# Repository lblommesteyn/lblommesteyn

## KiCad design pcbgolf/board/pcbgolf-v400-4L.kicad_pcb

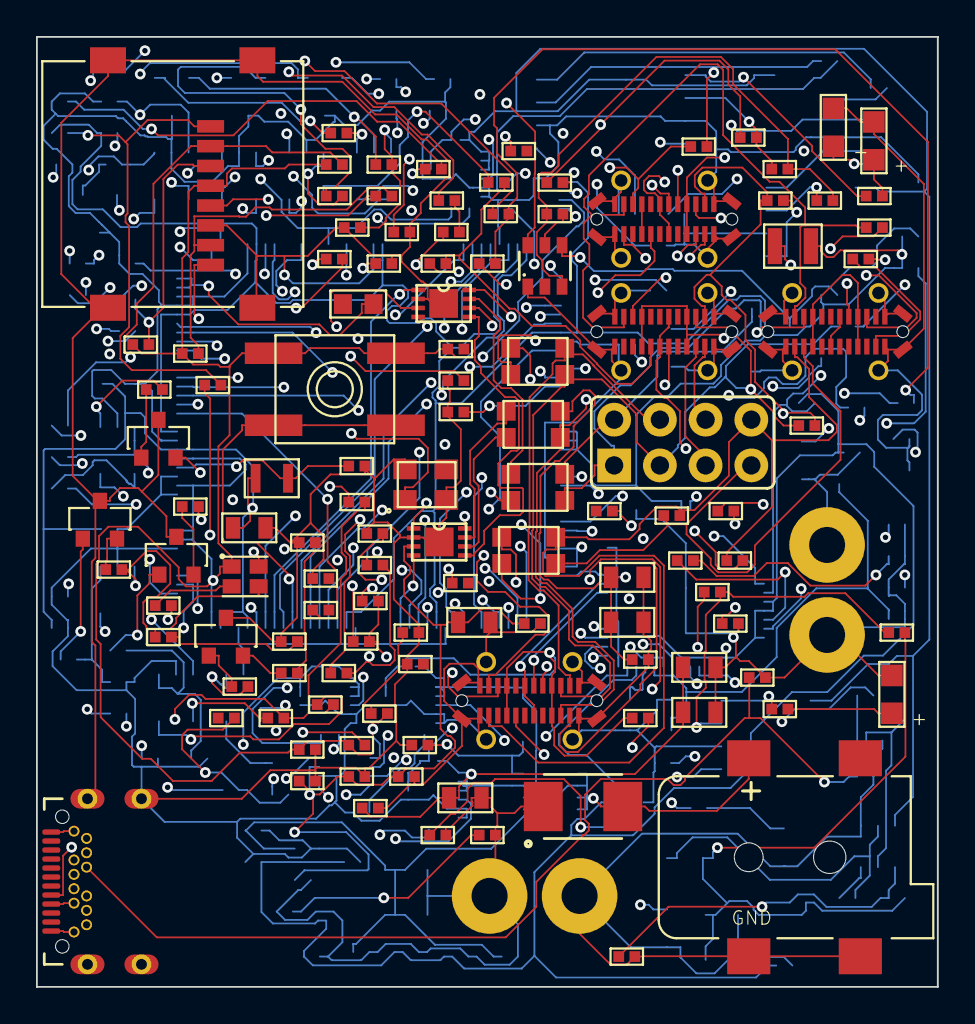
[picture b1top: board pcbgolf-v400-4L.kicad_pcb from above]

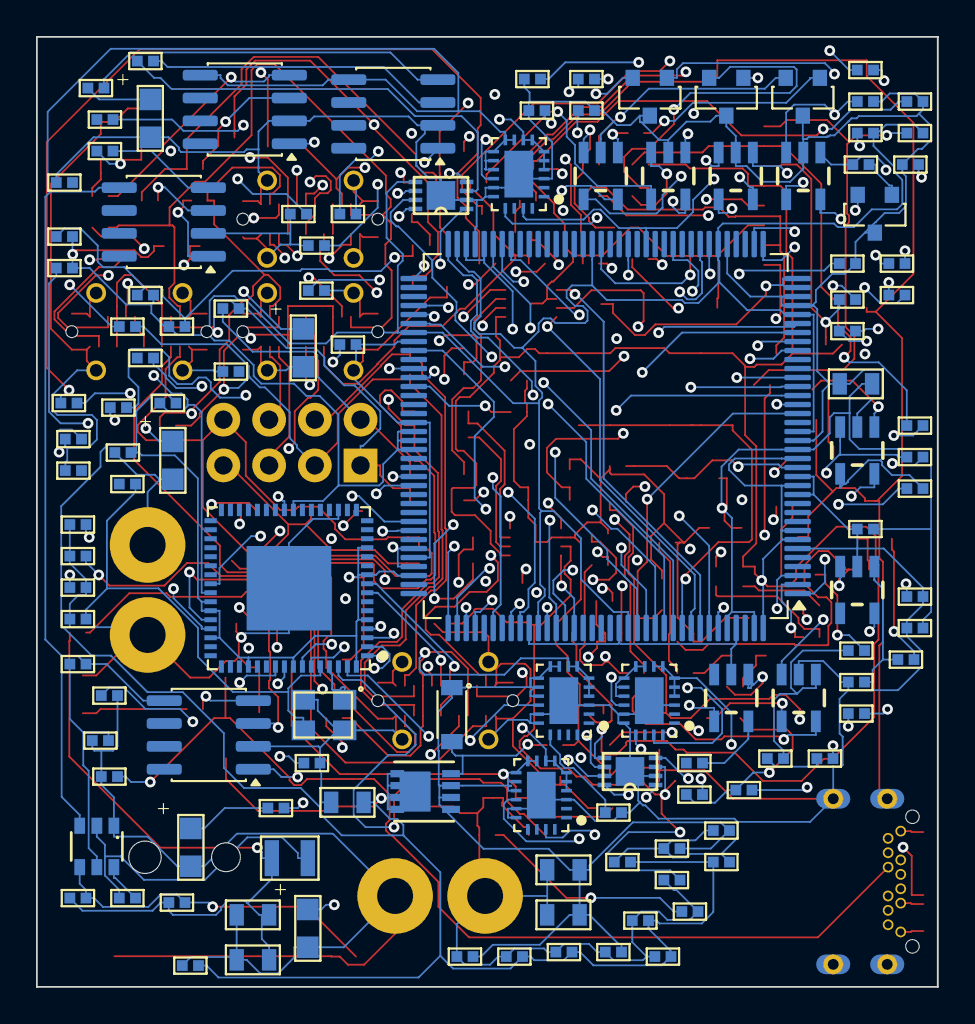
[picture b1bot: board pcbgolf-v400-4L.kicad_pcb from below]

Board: 4 copper layers, 50.0 x 52.8 mm, 245 parts (123 on the bottom side), 196 nets.

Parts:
BH1, BH2, BH3, BH4: M2_BOLT
C1, C3, C8, C12, C13, C15, C19, C20, C21: 10uF; 0805-C
C2, C4, C5, C7, C9, C11, C16, C18, C22, C23, C24, C26, C27, C30, C31, C35, C36, C38, C39, C40, C41, C42, C43, C44, C45, C46, C47, C48, C49: 100nF; 0402-C
C6, C10: DNP; 0402-C
C14, C17, C28, C32: 12pF; 0402-C
C25: 220pF; 0402-C
C29, C33, C34, C37: 10u; 0402-C
C50, C51, C52, C53: 10u; 0805-C
D1: TVS-BI-DO214AA; DO-214AA(SMB)
D2: DIODEDB2W40100L; SOD-123F
J1: DCBARRELSMT; DCJACK_2MM_SMT
J2: MICRO_SD-0472192001; 0472192001
J3: USB-C-FEMALE; DX07S024XJ1R1100
J4: CAN; 2X04
J5, J6, J7, J8: USB-C-FEMALEGCT; USB-C-FEMALE-VERT-GCT
L1, L2: 3u3; L-1008
L3: L-US-L2; 0603-L
L4: 2u2; 0806
L5, L6, L7, L8: ACT1210D_CHOKE; CHOKE-3.2X2.5
LED1: CREE-RGB-CLMVC
LED2: CAN0; CHIPLED
LED3: CAN1; CHIPLED
LED4: CAN2; CHIPLED
LED5: CAN3; CHIPLED
LED6, LED7, LED8, LED9: CH1_PWR; CHIPLED
LED10, LED11, LED12, LED13, LED14, LED15, LED16, LED17: LED-CC-GREEN-RED-AM23ESG; SOT23-3
Q1: SIS427-VI; PP-1212-8
Q2, Q3, Q4, Q5, Q6, Q7, Q8, Q9: NFET-DUAL-COMMON-SOURCE-QS5K2; SOT23-5
R1, R3, R7, R8, R9, R11, R12, R28, R29, R30, R31, R32, R33, R34, R35, R36, R37, R44, R45, R50, R51, R53, R54, R56, R57, R59, R60, R78, R79, R80, R81, R98, R99, R100, R101, R102, R103, R104, R105, R122, R123, R124, R125: 10k; 0402-R
R2, R21, R23, R90, R92, R94, R96, R114, R116, R118, R120: 1k; 0402-R
R4, R5, R6, R13, R14, R15, R16, R17, R18, R19, R20, R24, R25, R52, R55, R58, R61: 100k; 0402-R
R10: 52k3; 0402-R
R22, R62, R63, R64, R65: 2k7; 0402-R
R26: 1M; 0402-R
R27: 12k; 0402-R
R38, R39, R40, R41, R42, R43: 0R; 0402-R
R46, R47, R48, R49: 60; 0402-R
R66, R67, R68, R69: 28k; 0402-R
R70, R71, R72, R73: 33k; 0402-R
R74, R75, R76, R77: 3k3; 0402-R
R82, R83, R84, R85, R86, R87, R88, R89, R91, R93, R95, R97, R106, R107, R108, R109, R110, R111, R112, R113, R115, R117, R119, R121: 100; 0402-R
SW1: SPST-2-4PIN; EVQ-Q2
U1, U2: AP62300T; SOT23-6
U3: STM32H725ZGTx; LQFP-144_20x20mm_P0.5mm
U4: USB2517; QFN64-9X9
U5, U6, U7, U8: MCP2542FDT-E/MNY; TDFN8_2X3MC_MCH
U9, U10, U11, U12: NCS20071XV; SOIC-8_3.9x4.9mm_P1.27mm
U13, U14, U15, U16: TPS25942; WQFN20
Y1: 25MHz; XTAL-3.2X2.5
Y2: 24MHz; XTAL-3.2X2.5

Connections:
+3V3: C6.2, C7.1, C8.1, C19.1, C20.1, C23.1, C24.1, C26.1, C27.1, C30.2, C31.2, C37.1, C42.1, C43.1, C44.1, C45.1, J2.4 (VDD), L1.2, L3.1, LED1.U1 (COM+), R4.1, R5.1, R6.1, R11.1, R28.1, R29.1, R30.1, R33.1, R34.1, R35.1, R36.1, R37.1, SW1.B (S), SW1.B' (S1), U3.7 (VDD), U3.8 (VBAT), U3.13 (VDD), U3.16 (VDDSMPS), U3.19 (VDD), U3.32 (VDD), U3.42 (VDD), U3.56 (VDD), U3.71 (VDD), U3.79 (VDD), U3.90 (VDD50USB), U3.91 (VDD33USB), U3.92 (VDD), U3.106 (VDD), U3.119 (VDD), U3.129 (VDD), U3.144 (VDD), U4.5 (VDDA33), U4.10 (VDDA33), U4.13 (CFG_SEL2), U4.24 (VDD33CR), U4.42 (CFG_SEL1), U4.43 (RESET_N), U4.46 (VDD33), U4.52 (VDDA33), U4.57 (VDDA33), U4.64 (VDD33PLL), U5.5 (VIO), U6.5 (VIO), U7.5 (VIO), U8.5 (VIO)
+5V: C1.1, C2.1, C10.2, C11.1, C12.1, C13.1, C38.1, C39.1, C40.1, C41.1, L2.2, R1.1, R10.2, R52.2, R55.2, R58.2, R61.2, U1.3 (IN), U5.3 (VDD), U6.3 (VDD), U7.3 (VDD), U8.3 (VDD)
+12V: C3.1, C5.1, C46.1, C47.1, C48.1, C49.1, C50.1, C51.1, C52.1, C53.1, D2.1 (C), Q1.1 (S), Q1.2 (S), Q1.3 (S), R7.1, U2.3 (IN), U9.5 (V+), U10.5 (V+), U11.5 (V+), U12.5 (V+), U13.9 (VIN), U13.10 (VIN), U13.11 (VIN), U13.12 (VIN), U13.13 (VIN), U14.9 (VIN), U14.10 (VIN), U14.11 (VIN), U14.12 (VIN), U14.13 (VIN), U15.9 (VIN), U15.10 (VIN), U15.11 (VIN), U15.12 (VIN), U15.13 (VIN), U16.9 (VIN), U16.10 (VIN), U16.11 (VIN), U16.12 (VIN), U16.13 (VIN)
BTN: R12.2, SW1.A, SW1.A' (P1), U3.65 (PE15), U3.135 (BOOT0)
CAN0_EN: U3.134 (PB7), U5.8 (STBY)
CAN0_H: J4.2, J5.A2 (TX1+), J6.A2 (TX1+), J7.A2 (TX1+), J8.A2 (TX1+), L5.4, R46.2, R50.1
CAN0_L: J4.1, J5.A3 (TX1-), J6.A3 (TX1-), J7.A3 (TX1-), J8.A3 (TX1-), L5.3, R46.1, R51.1
CAN0_RX: U3.136 (PB8), U5.4 (RXD)
CAN0_TX: U3.137 (PB9), U5.1 (TXD)
CAN1_EN: U3.130 (PB3(JTDO), U6.8 (STBY)
CAN1_H: J4.4, J5.A11 (RX2+), J6.A11 (RX2+), J7.A11 (RX2+), J8.A11 (RX2+), L6.4, R47.2, R53.1
CAN1_L: J4.3, J5.A10 (RX2-), J6.A10 (RX2-), J7.A10 (RX2-), J8.A10 (RX2-), L6.3, R47.1, R54.1
CAN1_RX: U3.132 (PB5), U6.4 (RXD)
CAN1_TX: U3.133 (PB6), U6.1 (TXD)
CAN2_EN: U3.121 (PD7), U7.8 (STBY)
CAN2_H: J4.6, J5.B2 (TX2+), J6.B2 (TX2+), J7.B2 (TX2+), J8.B2 (TX2+), L7.4, R48.2, R56.1
CAN2_L: J4.5, J5.B3 (TX2-), J6.B3 (TX2-), J7.B3 (TX2-), J8.B3 (TX2-), L7.3, R48.1, R57.1
CAN2_RX: U3.123 (PG10), U7.4 (RXD)
CAN2_TX: U3.122 (PG9), U7.1 (TXD)
CAN3_EN: U3.131 (PB4(NJTRST)), U8.8 (STBY)
CAN3_H: J4.8, J5.B11 (RX1+), J6.B11 (RX1+), J7.B11 (RX1+), J8.B11 (RX1+), L8.4, R49.2, R59.1
CAN3_L: J4.7, J5.B10 (RX1-), J6.B10 (RX1-), J7.B10 (RX1-), J8.B10 (RX1-), L8.3, R49.1, R60.1
CAN3_RX: U3.72 (PB12), U8.4 (RXD)
CAN3_TX: U3.73 (PB13), U8.1 (TXD)
CH1_D_N: J5.A7 (D-A), J5.B7 (D-B), U4.1 (USBDN1_DM)
CH1_D_P: J5.A6 (D+A), J5.B6 (D+B), U4.2 (USBDN1_DP)
CH1_IMON: R70.2, U3.47 (PC4), U13.19 (IMON)
CH1_PWR_EN: U3.37 (PA0), U13.14 (EN)
CH1_SBU1: J5.A8 (SBU1), R19.2, R90.2, R91.2
CH1_SBU1_IGN: Q2.1 (G1), R78.1, R83.2, U3.112 (PD0)
CH1_SBU1_RELAY: Q2.3 (G2), R82.2, R98.2, U3.113 (PD1)
CH1_SBU2: J5.B8 (SBU2), R20.2, R114.2, R115.2
CH1_SBU2_IGN: Q6.1 (G1), R102.1, R107.2, U3.115 (PD3)
CH1_SBU2_RELAY: Q6.3 (G2), R106.2, R122.2, U3.116 (PD4)
CH2_D_N: J6.A7 (D-A), J6.B7 (D-B), U4.3 (USBDN2_DM)
CH2_D_P: J6.A6 (D+A), J6.B6 (D+B), U4.4 (USBDN2_DP)
CH2_IMON: R71.2, U3.50 (PB1), U14.19 (IMON)
CH2_PWR_EN: U3.38 (PA1), U14.14 (EN)
CH2_SBU1: J6.A8 (SBU1), R15.2, R92.2, R93.2
CH2_SBU1_IGN: Q3.1 (G1), R79.1, R85.2, U3.117 (PD5)
CH2_SBU1_RELAY: Q3.3 (G2), R84.2, R99.2, U3.120 (PD6)
CH2_SBU2: J6.B8 (SBU2), R13.2, R116.2, R117.2
CH2_SBU2_IGN: Q7.1 (G1), R103.1, R109.2, U3.76 (PD8)
CH2_SBU2_RELAY: Q7.3 (G2), R108.2, R123.2, U3.78 (PD10)
CH3_D_N: J7.A7 (D-A), J7.B7 (D-B), U4.6 (USBDN3_DM)
CH3_D_P: J7.A6 (D+A), J7.B6 (D+B), U4.7 (USBDN3_DP)
CH3_IMON: R72.2, U3.52 (PF11), U15.19 (IMON)
CH3_PWR_EN: U3.43 (PA4), U15.14 (EN)
CH3_SBU1: J7.A8 (SBU1), R17.2, R94.2, R95.2
CH3_SBU1_IGN: Q4.1 (G1), R80.1, R87.2, U3.82 (PD12)
CH3_SBU1_RELAY: Q4.3 (G2), R86.2, R100.2, U3.81 (PD11)
CH3_SBU2: J7.B8 (SBU2), R18.2, R118.2, R119.2
CH3_SBU2_IGN: Q8.1 (G1), R104.1, R111.2, U3.77 (PD9)
CH3_SBU2_RELAY: Q8.3 (G2), R110.2, R124.2, U3.83 (PD13)
CH4_D_N: J8.A7 (D-A), J8.B7 (D-B), U4.8 (USBDN4_DM)
CH4_D_P: J8.A6 (D+A), J8.B6 (D+B), U4.9 (USBDN4_DP)
CH4_IMON: R73.2, U3.45 (PA6), U16.19 (IMON)
CH4_PWR_EN: U3.44 (PA5), U16.14 (EN)
CH4_SBU1: J8.A8 (SBU1), R16.2, R96.2, R97.2
CH4_SBU1_IGN: Q5.1 (G1), R81.1, R89.2, U3.84 (PD14)
CH4_SBU1_RELAY: Q5.3 (G2), R88.2, R101.2, U3.85 (PD15)
CH4_SBU2: J8.B8 (SBU2), R14.2, R120.2, R121.2
CH4_SBU2_IGN: Q9.1 (G1), R105.1, R113.2, U3.138 (PE0)
CH4_SBU2_RELAY: Q9.3 (G2), R112.2, R125.2, U3.139 (PE1)
GND: BH1.0 (1_0), BH2.0 (1_0), BH3.0 (1_0), BH4.0 (1_0), C1.2, C2.2, C3.2, C5.2, C7.2, C8.2, C11.2, C12.2, C13.2, C14.2, C15.2, C16.2, C17.2, C18.2, C19.2, C20.2, C21.2, C22.2, C23.2, C24.2, C25.2, C26.2, C27.2, C28.2, C29.2, C30.1, C31.1, C32.2, C33.2, C34.2, C35.1, C36.1, C37.2, C38.2, C39.2, C40.2, C41.2, C42.2, C43.2, C44.2, C45.2, C46.2, C47.2, C48.2, C49.2, C50.2, C51.2, C52.2, C53.2, D1.1, J1.GND (GNDBREAK), J1.GNDBREAK (GND), J2.6 (VSS), J2.G1 (GND), J2.G2 (GND), J2.G3 (GND), J2.G4 (GND), J3.A1 (GND), J3.A12 (GND), J3.B1 (GND), J3.B1T (GND), J3.B12 (GND), J3.B12T (GND), J3.S1B (SHIELDA), J3.S1T (SHIELDA), J3.S1TH (SHIELDA), J3.S2B (SHIELDA), J3.S2T (SHIELDA), J3.S2TH (SHIELDA), J3.S3B (SHIELDB), J3.S3T (SHIELDB), J3.S3TH (SHIELDB), J3.S4B (SHIELDB), J3.S4T (SHIELDB), J3.S4TH (SHIELDB), J5.A1 (GND), J5.A12 (GND), J5.B1 (GND), J5.B12 (GND), J5.S1 (SHIELDA), J5.S2 (SHIELDA), J5.S3 (SHIELDA), J5.S4 (SHIELDA), J5.S11 (SHIELDB), J5.S12 (SHIELDB), J5.S13 (SHIELDB), J5.S14 (SHIELDB), J6.A1 (GND), J6.A12 (GND), J6.B1 (GND), J6.B12 (GND), J6.S1 (SHIELDA), J6.S2 (SHIELDA), J6.S3 (SHIELDA), J6.S4 (SHIELDA), J6.S11 (SHIELDB), J6.S12 (SHIELDB), J6.S13 (SHIELDB), J6.S14 (SHIELDB), J7.A1 (GND), J7.A12 (GND), J7.B1 (GND), J7.B12 (GND), J7.S1 (SHIELDA), J7.S2 (SHIELDA), J7.S3 (SHIELDA), J7.S4 (SHIELDA), J7.S11 (SHIELDB), J7.S12 (SHIELDB), J7.S13 (SHIELDB), J7.S14 (SHIELDB), J8.A1 (GND), J8.A12 (GND), J8.B1 (GND), J8.B12 (GND), J8.S1 (SHIELDA), J8.S2 (SHIELDA), J8.S3 (SHIELDA), J8.S4 (SHIELDA), J8.S11 (SHIELDB), J8.S12 (SHIELDB), J8.S13 (SHIELDB), J8.S14 (SHIELDB), LED2.C, LED3.C, LED4.C, LED5.C, LED6.C, LED7.C, LED8.C, LED9.C, LED10.3 (C), LED11.3 (C), LED12.3 (C), LED13.3 (C), LED14.3 (C), LED15.3 (C), LED16.3 (C), LED17.3 (C), Q2.2 (S), Q3.2 (S), Q4.2 (S), Q5.2 (S), Q6.2 (S), Q7.2 (S), Q8.2 (S), Q9.2 (S), R2.1, R3.2, R8.2, R9.2, R12.1, R25.1, R27.1, R31.2, R32.2, R44.2, R45.2, R66.1, R67.1, R68.1, R69.1, R70.1, R71.1, R72.1, R73.1, R78.2, R79.2, R80.2, R81.2, R98.1, R99.1, R100.1, R101.1, R102.2, R103.2, R104.2, R105.2, R122.1, R123.1, R124.1, R125.1, U1.1 (GND), U2.1 (GND), U3.6 (VSS), U3.12 (VSS), U3.14 (VSSSMPS), U3.18 (VSS), U3.33 (VSS), U3.34 (VSSA), U3.41 (VSS), U3.55 (VSS), U3.69 (VSS), U3.80 (VSS), U3.89 (VSS), U3.104 (VSS), U3.118 (VSS), U3.128 (VSS), U3.141 (VSS), U4.19 (TEST), U4.PAD (VSS), U5.2 (VSS), U5.PAD (EPAD), U6.2 (VSS), U6.PAD (EPAD), U7.2 (VSS), U7.PAD (EPAD), U8.2 (VSS), U8.PAD (EPAD), U9.2 (V-), U10.2 (V-), U11.2 (V-), U12.2 (V-), U13.3 (PGTH), U13.15 (OVP), U13.16 (GND), U13.PAD (GND), U14.3 (PGTH), U14.15 (OVP), U14.16 (GND), U14.PAD (GND), U15.3 (PGTH), U15.15 (OVP), U15.16 (GND), U15.PAD (GND), U16.3 (PGTH), U16.15 (OVP), U16.16 (GND), U16.PAD (GND), Y1.2 (3), Y1.4 (3), Y2.2 (3), Y2.4 (3)
HUB_SCL: R30.2, U3.66 (PB10), U4.41 (SCL)
HUB_SDA: R28.2, U3.67 (PB11), U4.40 (SDA)
LED_B: R23.2, U3.1 (PE2)
LED_G: R22.2, U3.2 (PE3)
LED_R: R21.2, U3.3 (PE4)
unnamed: D1.2, J1.PWR1 (PWR), Q1.5 (D), Q1.6 (D), Q1.7 (D), Q1.8 (D), Q1.9 (D)
unnamed: C9.1, U2.6 (BST)
unnamed: C9.2, L2.1, U2.2 (SW)
unnamed: R1.2, U1.5 (EN)
unnamed: C4.2, L1.1, U1.2 (SW)
unnamed: C6.1, R3.1, R4.2, R5.2, R6.2, U1.4 (FB)
unnamed: C4.1, U1.6 (BST)
unnamed: D2.2 (A), Q1.4 (G), R2.2
unnamed: R7.2, R8.1, U2.5 (EN)
unnamed: C10.1, R9.1, R10.1, U2.4 (FB)
unnamed: LED1.U2 (R-), R21.1
unnamed: LED1.U3 (G-), R22.1
unnamed: LED1.U4 (B-), R23.1
unnamed: C14.1, U3.25 (PH0), Y1.1
unnamed: R13.1, U3.21 (PF7)
unnamed: R14.1, U3.22 (PF8)
unnamed: R15.1, U3.23 (PF9)
unnamed: R16.1, U3.24 (PF10)
unnamed: C17.1, U3.26 (PH1), Y1.3 (2)
unnamed: R17.1, U3.28 (PC0)
unnamed: R18.1, U3.29 (PC1)
unnamed: R19.1, U3.30 (PC2_C)
unnamed: R20.1, U3.31 (PC3_C)
unnamed: R11.2, U3.142 (PDR_ON)
unnamed: C33.1, C35.2, U4.25 (VDD18)
unnamed: R24.1, R25.2, U4.44 (VBUS_DET)
unnamed: R29.2, U4.45 (SUSP_IND)
unnamed: C32.1, R26.1, U4.60 (XTAL2), Y2.3 (2)
unnamed: C28.1, R26.2, U4.61 (XTAL1), Y2.1
unnamed: C34.1, C36.2, U4.62 (VDD18PLL)
unnamed: R27.2, U4.63 (RBIAS)
unnamed: J3.A5 (CC1), R31.1, R32.1
unnamed: J3.B2 (TX2+), J3.B2T (TX2+)
unnamed: J3.B3 (TX2-), J3.B3T (TX2-)
unnamed: J3.B5 (CC2), J3.B5T (CC2), R44.1, R45.1
unnamed: J3.B8 (SBU2), J3.B8T (SBU2)
unnamed: J3.B10 (RX1-), J3.B10T (RX1-)
unnamed: J3.B11 (RX1+), J3.B11T (RX1+)
unnamed: J2.7 (DAT0), R33.2, R38.2
unnamed: J2.8 (DAT1), R34.2, R39.2
unnamed: J2.2 (CD/DAT3), R36.2, R41.2
unnamed: J2.3 (CMD), R37.2, R42.2
unnamed: J2.1 (DAT2), R35.2, R40.2
unnamed: J2.5 (CLK), R43.2
unnamed: R64.1, U11.4
unnamed: LED4.A, R64.2
unnamed: R50.2, U9.1 (+)
unnamed: R51.2, R52.1, U9.3 (-)
unnamed: R62.1, U9.4
unnamed: LED2.A, R62.2
unnamed: R57.2, R58.1, U11.3 (-)
unnamed: LED3.A, R63.2
unnamed: R56.2, U11.1 (+)
unnamed: LED5.A, R65.2
unnamed: L8.1, U8.7 (CANH)
unnamed: L8.2, U8.6 (CANL)
unnamed: R65.1, U12.4
unnamed: R53.2, U10.1 (+)
unnamed: R54.2, R55.1, U10.3 (-)
unnamed: R63.1, U10.4
unnamed: R59.2, U12.1 (+)
unnamed: L7.2, U7.6 (CANL)
unnamed: L7.1, U7.7 (CANH)
unnamed: L5.2, U5.6 (CANL)
unnamed: L5.1, U5.7 (CANH)
unnamed: R60.2, R61.1, U12.3 (-)
unnamed: L6.2, U6.6 (CANL)
unnamed: L6.1, U6.7 (CANH)
unnamed: J7.A4 (VBUS), J7.A9 (VBUS), J7.B4 (VBUS), J7.B9 (VBUS), R76.1, U15.4 (VOUT), U15.5 (VOUT), U15.6 (VOUT), U15.7 (VOUT), U15.8 (VOUT)
unnamed: Q2.4 (D2), R91.1
unnamed: Q2.5 (D1), R90.1
unnamed: Q3.4 (D2), R93.1
unnamed: J5.A4 (VBUS), J5.A9 (VBUS), J5.B4 (VBUS), J5.B9 (VBUS), R74.1, U13.4 (VOUT), U13.5 (VOUT), U13.6 (VOUT), U13.7 (VOUT), U13.8 (VOUT)
unnamed: R66.2, U13.17 (ILIM)
unnamed: J6.A4 (VBUS), J6.A9 (VBUS), J6.B4 (VBUS), J6.B9 (VBUS), R75.1, U14.4 (VOUT), U14.5 (VOUT), U14.6 (VOUT), U14.7 (VOUT), U14.8 (VOUT)
unnamed: R67.2, U14.17 (ILIM)
unnamed: R68.2, U15.17 (ILIM)
unnamed: Q5.5 (D1), R96.1
unnamed: Q9.4 (D2), R121.1
unnamed: Q9.5 (D1), R120.1
unnamed: J8.A4 (VBUS), J8.A9 (VBUS), J8.B4 (VBUS), J8.B9 (VBUS), R77.1, U16.4 (VOUT), U16.5 (VOUT), U16.6 (VOUT), U16.7 (VOUT), U16.8 (VOUT)
unnamed: LED9.A, R77.2
unnamed: LED14.1 (AR), R107.1
unnamed: LED14.2 (AG), R106.1
unnamed: LED15.1 (AR), R109.1
unnamed: LED15.2 (AG), R108.1
unnamed: Q7.4 (D2), R117.1
unnamed: Q7.5 (D1), R116.1
unnamed: LED8.A, R76.2
unnamed: LED7.A, R75.2
unnamed: LED16.2 (AG), R110.1
unnamed: LED11.1 (AR), R85.1
unnamed: LED11.2 (AG), R84.1
unnamed: Q6.4 (D2), R115.1
unnamed: LED17.2 (AG), R112.1
unnamed: Q6.5 (D1), R114.1
unnamed: R69.2, U16.17 (ILIM)
unnamed: LED13.1 (AR), R89.1
unnamed: Q8.4 (D2), R119.1
unnamed: Q8.5 (D1), R118.1
unnamed: LED6.A, R74.2
unnamed: LED16.1 (AR), R111.1
unnamed: LED10.1 (AR), R83.1
unnamed: LED10.2 (AG), R82.1
unnamed: Q5.4 (D2), R97.1
unnamed: Q4.5 (D1), R94.1
unnamed: LED17.1 (AR), R113.1
unnamed: LED13.2 (AG), R88.1
unnamed: Q4.4 (D2), R95.1
unnamed: LED12.1 (AR), R87.1
unnamed: LED12.2 (AG), R86.1
unnamed: Q3.5 (D1), R92.1
SD_CLK: R43.1, U3.111 (PC12)
SD_CMD: R42.1, U3.114 (PD2)
SD_D0: R38.1, U3.95 (PC8)
SD_D1: R39.1, U3.96 (PC9)
SD_D2: R40.1, U3.109 (PC10)
SD_D3: R41.1, U3.110 (PC11)
STM_D_N: U3.100 (PA11), U4.55 (USBDN7_DM)
STM_D_P: U3.101 (PA12), U4.56 (USBDN7_DP)
USB_D_N: J3.A7 (D-A), J3.B7 (D-B), J3.B7T (D-B), U4.58 (USBUP_DM)
USB_D_P: J3.A6 (D+A), J3.B6 (D+B), J3.B6T (D+B), U4.59 (USBUP_DP)
VBUS: C29.1, J3.A4 (VBUS), J3.A9 (VBUS), J3.B4 (VBUS), J3.B4T (VBUS), J3.B9 (VBUS), J3.B9T (VBUS), R24.2
VDDA: C22.1, L3.2, U3.35 (VREF+), U3.36 (VDDA)
VDDLDO: C15.1, C16.1, C18.1, C21.1, L4.1, U3.17 (VFBSMPS), U3.68 (VCAP), U3.70 (VDDLDO), U3.103 (VCAP), U3.105 (VDDLDO), U3.140 (VCAP), U3.143 (VDDLDO)
VLXSMPS: C25.1, L4.2, U3.15 (VLXSMPS)

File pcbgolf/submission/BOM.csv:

qty,refs,value,orig_footprint,orig_mpn,new_footprint,new_part,risk,rationale
43,R1 R100 R101 R102 R103 R104 R105 R11 R12 R122 R123 R124 R125 R28 R29 R3 R30 R31 R32 R33 R34 R35 R36 R37 R44 R45 R50 R51 R53 R54 R56 R57 R59 R60 R7 R78 R79 R8 R80 R81 R9 R98 R99,10k,0402-R,RC0402FR-0710KL,0201-R,0201 thick-film,low,JLCPCB assembles 0201; all resistor values available
29,C11 C16 C18 C2 C22 C23 C24 C26 C27 C30 C31 C35 C36 C38 C39 C4 C40 C41 C42 C43 C44 C45 C46 C47 C48 C49 C5 C7 C9,100nF,0402-C,CL05F104ZO5NNNC,0201-C,0201 X5R/X7R,low,100nF/12pF/220pF fine in 0201; keep 10uF at 0402
24,R106 R107 R108 R109 R110 R111 R112 R113 R115 R117 R119 R121 R82 R83 R84 R85 R86 R87 R88 R89 R91 R93 R95 R97,100,0402-R,RC0402JR-07100RL,0201-R,0201 thick-film,low,JLCPCB assembles 0201; all resistor values available
17,R13 R14 R15 R16 R17 R18 R19 R20 R24 R25 R4 R5 R52 R55 R58 R6 R61,100k,0402-R,RC0402JR-07100KL,0201-R,0201 thick-film,low,JLCPCB assembles 0201; all resistor values available
11,R114 R116 R118 R120 R2 R21 R23 R90 R92 R94 R96,1k,0402-R,RC0402JR-071KL,0201-R,0201 thick-film,low,JLCPCB assembles 0201; all resistor values available
9,C1 C12 C13 C15 C19 C20 C21 C3 C8,10uF,0805-C,CL21A106KAYNNNE,0603-C,0603 10uF 25V X5R,low,10uF 0603 widely stocked; derate check on 12V rail
8,LED10 LED11 LED12 LED13 LED14 LED15 LED16 LED17,LED-CC-GREEN-RED-AM23ESG,SOT23-3,AM23ESGW,SOT23-3,(unchanged),-,
8,Q2 Q3 Q4 Q5 Q6 Q7 Q8 Q9,NFET-DUAL-COMMON-SOURCE-QS5K2,SOT23-5,QS5K2TR,SOT23-5,(unchanged),-,
6,R38 R39 R40 R41 R42 R43,0R,0402-R,RMCF0402ZT0R00,0201-R,0201 thick-film,low,JLCPCB assembles 0201; all resistor values available
5,R22 R62 R63 R64 R65,2k7,0402-R,RC0402JR-072K7L,0201-R,0201 thick-film,low,JLCPCB assembles 0201; all resistor values available
4,C14 C17 C28 C32,12pF,0402-C,C0402C120J5GACTU,0201-C,0201 X5R/X7R,low,100nF/12pF/220pF fine in 0201; keep 10uF at 0402
4,C29 C33 C34 C37,10u,0402-C,GRM155R61A106ME11D,0201-C,0201 X5R/X7R,low,100nF/12pF/220pF fine in 0201; keep 10uF at 0402
4,R70 R71 R72 R73,33k,0402-R,RC0402JR-0733KL,0201-R,0201 thick-film,low,JLCPCB assembles 0201; all resistor values available
4,R74 R75 R76 R77,3k3,0402-R,RC0402JR-073K3L,0201-R,0201 thick-film,low,JLCPCB assembles 0201; all resistor values available
4,R66 R67 R68 R69,28k,0402-R,RK73H1ETTP2802F,0201-R,0201 thick-film,low,JLCPCB assembles 0201; all resistor values available
4,R46 R47 R48 R49,60,0402-R,RC0402FR-0760R4L,0201-R,0201 thick-film,low,JLCPCB assembles 0201; all resistor values available
4,C50 C51 C52 C53,10u,0805-C,CL21A106KAYNNNE,0603-C,0603 10uF 25V X5R,low,10uF 0603 widely stocked; derate check on 12V rail
4,LED6 LED7 LED8 LED9,CH1_PWR,CHIPLED,LG R971-KN-1,CHIPLED,(unchanged),-,
4,L5 L6 L7 L8,ACT1210D_CHOKE,CHOKE-3.2X2.5,ACT1210D-101-2P-TL00,CHOKE-3.2X2.5,(unchanged),-,
4,BH1 BH2 BH3 BH4,M2_BOLT,M2_BOLT,,M2_BOLT,(unchanged),-,
4,U10 U11 U12 U9,NCS20071XV,SOIC-8_3.9x4.9mm_P1.27mm,NCS20071SN2T1G,SC70-5,NCS20071XV5T2G,none,"SAME die in SC-70-5. The schematic symbol is literally named ""NCS20071XV"" but the fitted MPN is the SOIC-8 SN2 part: free 33 mm^2 each."
4,U5 U6 U7 U8,MCP2542FDT-E/MNY,TDFN8_2X3MC_MCH,MCP2542FDT-H/MNY,TDFN8_2X3MC_MCH,(unchanged),-,
4,J5 J6 J7 J8,USB-C-FEMALEGCT,USB-C-FEMALE-VERT-GCT,10132328-10011LF,USB-C-MIDMOUNT,mid-mount USB-C (board in cutout),med,3.26mm body straddles PCB: ~1.85 above / ~1.4 below
4,U13 U14 U15 U16,TPS25942,WQFN20,TPS25944ARVCR,WQFN20,(unchanged),-,
2,C10 C6,DNP,0402-C,,0201-C,0201 X5R/X7R,low,100nF/12pF/220pF fine in 0201; keep 10uF at 0402
2,L1 L2,3u3,L-1008,MEKK2520T3R3M,L-1008,(unchanged),-,
2,U1 U2,AP62300T,SOT23-6,AP62300WU-7,SOT23-6,(unchanged),-,
1,C25,220pF,0402-C,04025A221FAT2A,0201-C,0201 X5R/X7R,low,100nF/12pF/220pF fine in 0201; keep 10uF at 0402
1,R27,12k,0402-R,CRGCQ0402F12K,0201-R,0201 thick-film,low,JLCPCB assembles 0201; all resistor values available
1,R26,1M,0402-R,RC0402JR-071ML,0201-R,0201 thick-film,low,JLCPCB assembles 0201; all resistor values available
1,R10,52k3,0402-R,RC0402FR-0752K3L,0201-R,0201 thick-film,low,JLCPCB assembles 0201; all resistor values available
1,J2,MICRO_SD-0472192001,0472192001,47219-2001,0472192001,(unchanged),-,
1,L3,L-US-L2,0603-L,MH1608-601Y,0603-L,(unchanged),-,
1,L4,2u2,0806,LQM2MPN2R2NG0L,0806,(unchanged),-,
1,J4,CAN,2X04,,2X04-RA,2.54mm 2x4 right-angle header,low,"same 2.54mm mating interface, lies down instead of up"
1,LED2,CAN0,CHIPLED,LG R971-KN-1,CHIPLED,(unchanged),-,
1,LED4,CAN2,CHIPLED,LG R971-KN-1,CHIPLED,(unchanged),-,
1,LED3,CAN1,CHIPLED,LG R971-KN-1,CHIPLED,(unchanged),-,
1,LED5,CAN3,CHIPLED,LG R971-KN-1,CHIPLED,(unchanged),-,
1,LED1,CREE-RGB-CLMVC,CREE-RGB-CLMVC,CLMVC-FKA-CL1D1L71BB7C3C3,CREE-RGB-CLMVC,(unchanged),-,
1,J1,DCBARRELSMT,DCJACK_2MM_SMT,PJ-002AH-SMT-TR,DCJACK-MIDMOUNT,2.0/5.5mm jack in PCB cutout,med,barrel centred on board plane: ~3.4 above / ~3.4 below
1,D1,TVS-BI-DO214AA,DO-214AA(SMB),SMAJ16CA-13-F,DO-214AA(SMB),(unchanged),-,
1,J3,USB-C-FEMALE,DX07S024XJ1R1100,DX07S024XJ1R1100,DX07S024XJ1R1100,(unchanged),-,
1,SW1,SPST-2-4PIN,EVQ-Q2,EVQ-Q2Y03W,EVQ-Q2,(unchanged),-,
1,U3,STM32H725ZGTx,LQFP-144_20x20mm_P0.5mm,STM32H725ZGT,LQFP-100_14x14,STM32H725VGT6,low,"same die/flash, 82 GPIO vs 50 needed; no escape vias"
1,Q1,SIS427-VI,PP-1212-8,SI7101DN-T1-GE3,PP-1212-8,(unchanged),-,
1,U4,USB2517,QFN64-9X9,USB2517,QFN64-9X9,(unchanged),-,
1,D2,DIODEDB2W40100L,SOD-123F,PMEG10020ELRX,SOD-123F,(unchanged),-,
1,Y2,24MHz,XTAL-3.2X2.5,ABM8AIG-24.000MHZ-12-2Z-T3,XTAL-3.2X2.5,(unchanged),-,
1,Y1,25MHz,XTAL-3.2X2.5,RH100-25.000-12-F-1010-TR,XTAL-3.2X2.5,(unchanged),-,
